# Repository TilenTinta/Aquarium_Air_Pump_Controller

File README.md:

# Aquarium_Air_Pump_Controller

Simple electronics for controlling aquarium air pump speed with some additional functions built around the WCH **CH32V003F4U6** MCU

---

## Table of Contents

- [Overview](#overview)
- [Features](#features)
  - [Hardware](#hardware)
  - [Software](#software)
- [Mounting](#mounting)
- [Flashing Firmware](#flashing-firmware)
- [Working device](#working-device)
  - [Working Principle](#working-principle)
- [Debugging](#debugging)
  - [LED Status Codes](#led-status-codes)

---

## Overview

This controller is a very compact solution for controling aquarium air pump speed. It is meant to be mounted on the back side of cheap chinese pumps that uses DC brushed motors like **PXYP370** and are powered from USB. By adjusting potenciometer on PCB you can tune pump speed and by that the amount of air provided in aquarium/filter. If you want to control this pump from external device like **ESP32** you can connect it over UART pads. This allow you to monitor and control the pump.

---

## Features

### Hardware

- **MCU:** WCH **CH32V003F4U6** with SWIO. 
- **Power:** Directly from 5V - USB.
- **Power regulation:** N-Channel MOSFET AP30N03DF.
- **Adjustment:** Duty cycle with potenciometer
- **Sensors:** Voltage IN, temperature.
- **Indicators/Controls:** Status LED and UART. 

### Software

- **Firmware:** C, developed in **MounRiver Studio IDE**. 
- **Updates:** **Custom bootloader** supports UART firmware updates. 

---

## Mounting

To mount controller on air pump you first need to remove silicon housing from the pump. Desolder both wires and bleed resistor from the motor contacts and clean them. Then solder the wires from USB cable to PCB. Correctly oriented pcb can be then soldered directly on motor contacts.

---

## Flashing Firmware

- Open the project in **MounRiver Studio IDE**, compile, and **upload** to the **CH32V003F4U6** MCU. 

> The board also includes a **custom bootloader** for **UART firmware updates** when supported by the desktop toolchain. 

---

## Working device

When USB cable is pluging the controler goes thrue start up routine. After that if everything is okay (input voltage, temperatue) it goes in running mode, otherwise it falls in error state which is indicated with **solid red light**.

### Working Principle

- **Sampling:** The system samples data at 50Hz*. In the first sample, the MCU collects raw measurements. In the next sample, these values are converted into real-world units (V, °C, %). This results in an effective sampling rate of 25Hz for the calculated values.
- **Control Logic:** Based on the collected values, the controller can either trigger an error or set a new duty cycle for the motor based on the potentiometer reading.
- **Error Conditions:**
    - **Over-temperature:** 80°C
    - **Under-voltage:** 3.5V
- **Duty Cycle:** The duty cycle can be set between 10% and 90%. Values below 10% are treated as 0%, and values above 90% are treated as 100%.
    - **Note:** This DC motors require a minimum of 3.0V - 3.5V to start.

---

## Debugging

### LED Status Codes  

| LED Pattern     | Meaning                   |
|-----------------|---------------------------|
| Blinking **red**  | Device initialization   |
| Solid **red**     | Device error            |

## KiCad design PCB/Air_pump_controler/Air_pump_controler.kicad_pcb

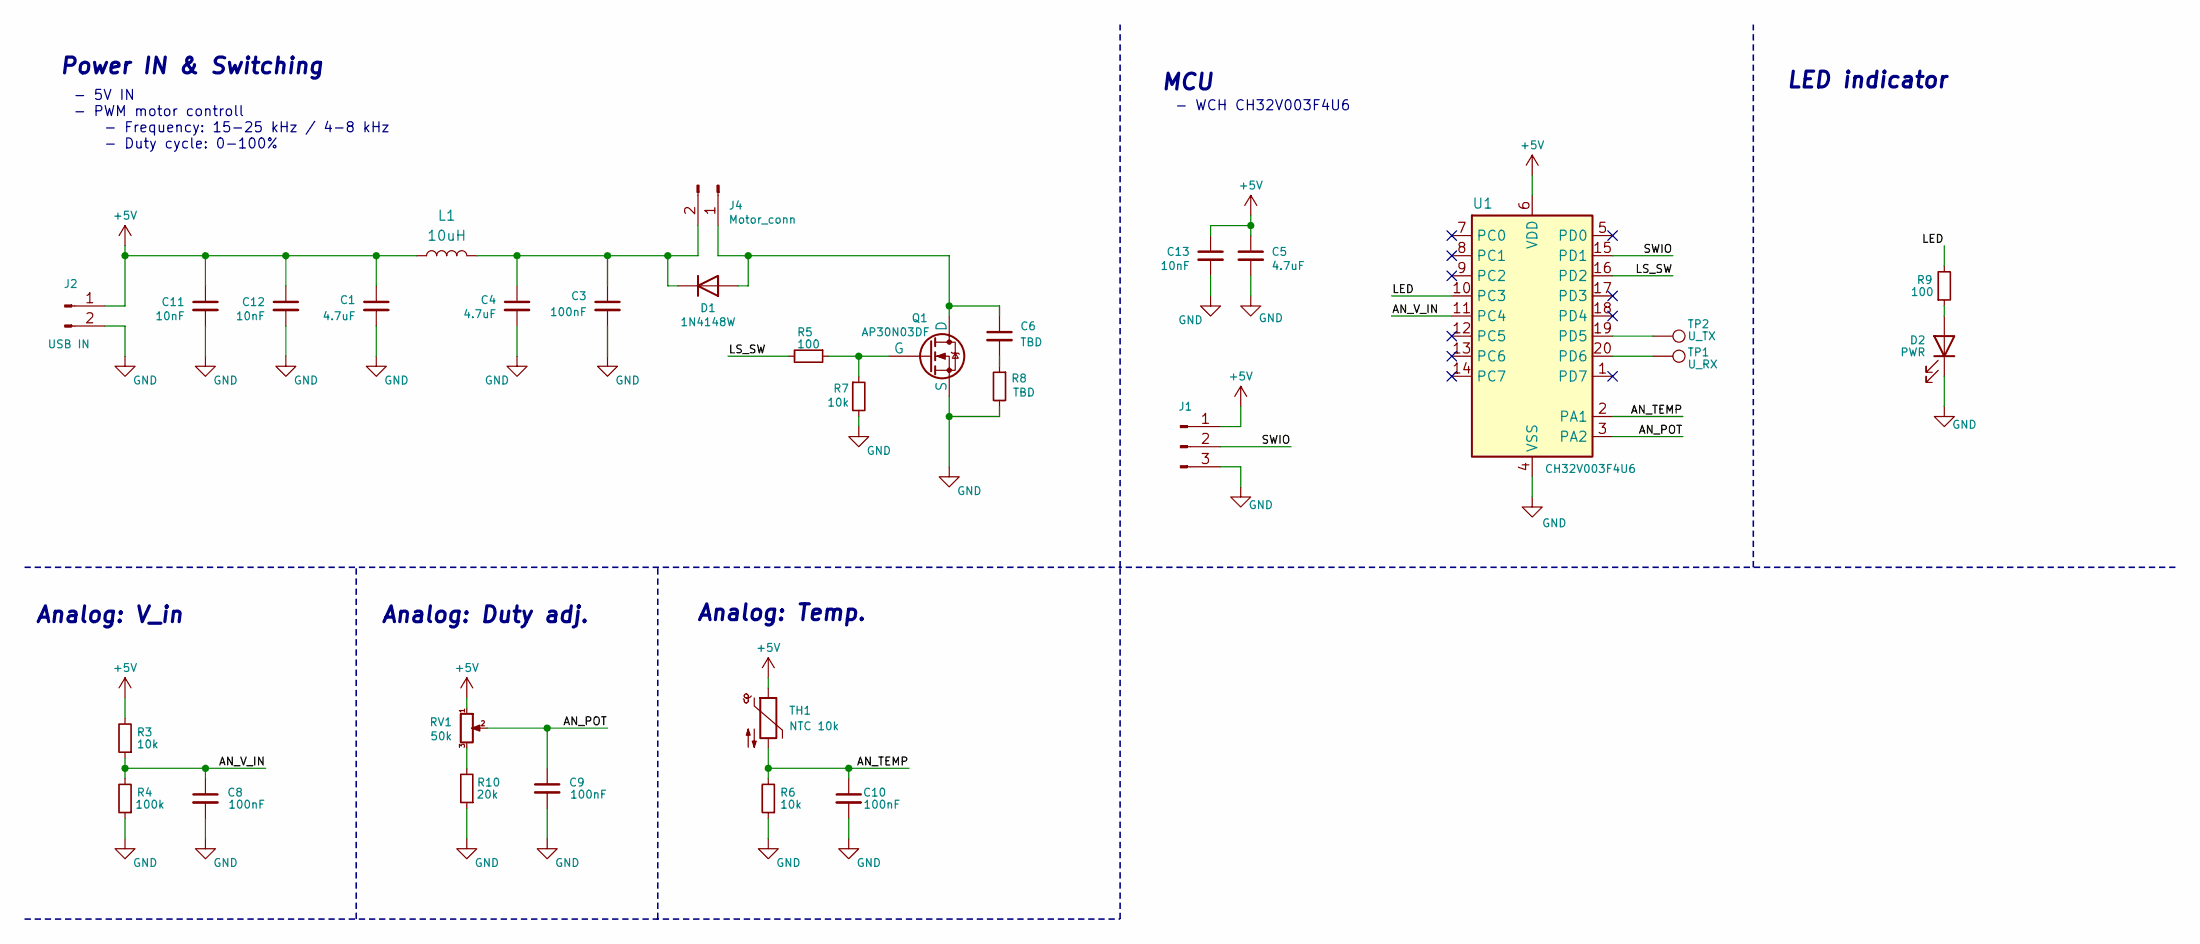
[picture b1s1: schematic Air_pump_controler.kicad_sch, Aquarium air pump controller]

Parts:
C1, C4: 4.7uF; C_1206_3216Metric
C3, C8, C9, C10: 100nF; C_0603_1608Metric
C5: 4.7uF; C_0402_1005Metric
C6: TBD; C_0603_1608Metric
C11, C12, C13: 10nF; C_0402_1005Metric
D1: 1N4148W; D_SOD-123
D2: PWR; LED_0603_1608Metric
J1: Conn_01x03_Pin; Samtec_UMPS-03-XX.X-X-V-S_1x03_P2.0mm_Socket
J2: USB IN; PinHeader_1x02_P2.54mm_Vertical
J4: Motor_conn
L1: 10uH; L_APV_APH0420
Q1: AP30N03DF
R3, R6, R7: 10k; R_0603_1608Metric
R4: 100k; R_0603_1608Metric
R5, R9: 100; R_0603_1608Metric
R8: TBD; R_0603_1608Metric
R10: 20k; R_0603_1608Metric
RV1: 50k; Potentiometer_Bourns_TC33X_Vertical
TH1: NTC 10k; R_0603_1608Metric
TP1: U_RX; TestPoint_Pad_D1.0mm
TP2: U_TX; TestPoint_Pad_D1.0mm
U1: CH32V003F4U6; QFN-20-1EP_3x3mm_P0.4mm_EP1.65x1.65mm

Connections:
+5V: C1.1, C5.1, C11.1, C12.1, C13.1, J1.1, J2.1, L1.1, R3.2, RV1.1, TH1.1, U1.6 (VDD)
/AN_POT: C9.1, RV1.2, U1.3 (PA2)
/AN_TEMP: C10.1, R6.2, TH1.2, U1.2 (PA1)
/AN_V_IN: C8.1, R3.1, R4.2, U1.11 (PC4)
/LED: R9.2, U1.10 (PC3)
/LS_SW: R5.2, U1.16 (PD2)
/SWIO: J1.2, U1.15 (PD1)
GND: C1.2, C3.2, C4.2, C5.2, C8.2, C9.2, C10.2, C11.2, C12.2, C13.2, D2.1 (K), J1.3, J2.2, Q1.1 (S), R4.1, R6.1, R7.2, R8.2, R10.1, U1.4 (VSS), U1.21 (VSS)
unnamed: C6.2, R8.1
unnamed: C6.1, D1.2 (A), J4.1, Q1.3 (D)
unnamed: C3.1, C4.1, D1.1 (K), J4.2, L1.2
unnamed: D2.2 (A), R9.1
unnamed: Q1.2 (G), R5.1, R7.1
unnamed: R10.2, RV1.3
unnamed 14: TP2.1, U1.19 (PD5); also elsewhere on the board
unnamed 15: TP1.1, U1.20 (PD6); also elsewhere on the board

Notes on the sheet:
Analog: Duty adj.
- 5V IN - PWM motor controll - Frequency: 15-25 kHz / 4-8 kHz - Duty cycle: 0-100%
LED indicator
Analog: Temp.
- WCH CH32V003F4U6
Analog: V_in
Power IN & Switching
MCU

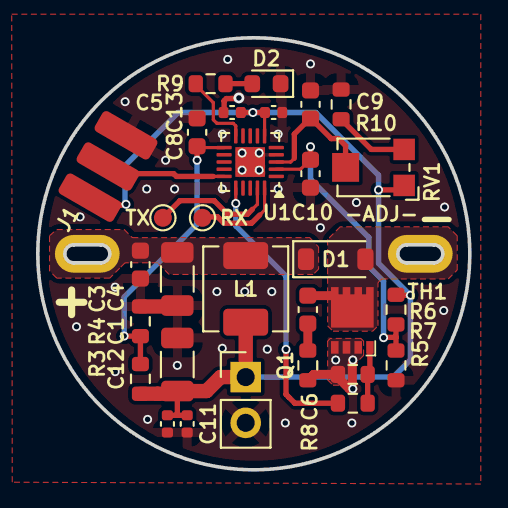
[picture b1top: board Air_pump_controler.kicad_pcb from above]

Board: 2 copper layers, 24.0 x 24.0 mm, 31 parts (0 on the bottom side), 16 nets.

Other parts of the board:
RX: U_RX; TestPoint_Pad_D1.0mm
TX: U_TX; TestPoint_Pad_D1.0mm

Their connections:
unnamed 14: TX.1; also elsewhere on the board
unnamed 15: RX.1; also elsewhere on the board

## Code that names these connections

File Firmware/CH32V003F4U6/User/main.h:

/***************************************************************************
 * File Name          : main.h
 * Author             : Tinta T.
 * Version            : V1.0.0
 * Date               : 2025/10/16
 * Description        : Main header file of Aquarium air pump controller
***************************************************************************/

#ifndef USER_MAIN_H_
#define USER_MAIN_H_

/* Includes */
#include <stdio.h>
#include <stdint.h>
#include <string.h>

/*###########################################################################################################################################################*/
/* Defines */

// Device constants
#define DEVICE_NAME    "Pump control"   // Name of the device
#define SW_VER              1           // Software version (used in UART packets)
#define SW_DATE        "October 2025"   // Date of software

#define OVER_TEMP           80          // Over temperature protection
#define BASE_VOLTAGE        500         // Expected voltage on the input
#define UNDER_VOLT          350         // Under voltage protection (3.5V)
#define MIN_DUTY            10          // Minimum value of duty cycle (lower is 0)
#define MAX_DUTY            90          // Maximum value of duty cycle (higher is 100)
#define V_IN_R1             10000       // Voltage divider (input voltage) R1 
#define V_IN_R2             100000      // Voltage divider (input voltage) R2 
#define DUTY_VREF           5           // Duty cycle ideal reference voltage
//#define DUTY_POT          20000       // Potenciometer (duty cycle), PCB Rev.: 0.1
#define DUTY_POT            50000       // Potenciometer (duty cycle), PCB Rev.: 0.2
#define DUTY_R              1800        // Resistor R2 (duty cycle), PCB Rev.: 0.2
#define TEMP_BETA           39500       // Voltage divider (temperature) NTC Beta value
#define TEMP_R0             10000       // R_0 value of NTC
#define TEMP_R              10000       // Voltage divider (temperature) R2 
#define TEMP_T_0            29815       // T_0 - reference temperature 25C / 298.15K

// Pinout
#define LED_RED             GPIO_Pin_3  // PC3: Pin of red LED
#define LS_SW               GPIO_Pin_2  // PD2: Low side switching mosfet
#define USART_TX            GPIO_Pin_5  // PD5: UART TX
#define USART_RX            GPIO_Pin_6  // PD6: UART RX
#define AN_V_IN             GPIO_Pin_4  // PC4: Analog read - USB voltage
#define ADC_CH_V_IN         ADC_Channel_2   // ADC Channel of PC4
#define AN_TEMP             GPIO_Pin_1  // PA1: Analog read - Temperature
#define ADC_CH_TEMP         ADC_Channel_1   // ADC Channel of PA1
#define AN_POT              GPIO_Pin_2  // PA2: Analog read - Potenciomeret voltage
#define ADC_CH_POT          ADC_Channel_0   // ADC Channel of PA2

/*###########################################################################################################################################################*/
/* Structs - marked with s at the beginning*/

typedef struct {
    uint8_t     bootDone;               // Flag: signal end of device initialization
    uint8_t     state;                  // Main state machine variable   
    uint8_t     analog_state;           // Analog read state machine variable  
    uint8_t     flag_analog_state;      // Flag used in IRQ for state monitoring
    uint8_t     flag_adc_read;          // Flag: read ADC value from current channel
    uint8_t     flag_overtemp;          // Flag: overtemperature protection
    uint8_t     flag_undervoltage;      // Flag: undervoltage protection
    uint16_t    duty;                   // Value if current duty cycle
} S_DEVICE;

typedef struct {            
    uint16_t    adcResults[3];          // buffer for ADC DMA results
    uint16_t    analogVoltage;          // Raw analog value of input voltage (10bit)
    uint16_t    analogTemperature;      // Raw analog value of temperature (10bit)
    uint16_t    analogPotenciometer;    // Raw analog value of potenciometer (10bit)
    uint16_t    voltage;                // Current value of input voltage
    uint16_t    temperature;            // Current value of temprature
    uint16_t    potVal;                 // Current value of potenciometer
    uint16_t    potPercent[10];         // Array of measurements from potenciometers
} S_ANALOG;


// Enumerate of states used in main state machine
enum eMainStates {
    devBoot,
    running,
    error
};

// Enumerate of states used in analog read state machine
enum eAnalogStates {
    ADCread,
    compute
};


#endif /* USER_MAIN_H_ */

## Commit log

2025-10-13 First commit
    PCB started, PCB edge
2025-10-14 Update
    PCB shematic and layout done rev.:0.1
2025-10-15 Finished PCB
2025-10-18 Readme
2025-10-18 Update
    readme
2025-10-19 Update
    software
2025-10-23 Update
    first FW complete, not tested on PCB
2025-11-02 Update
    pcb assembled, firmware works, added images
2025-11-05 Update
    modified potenciometer to voltage divider
2025-11-05 Update
    updated shematic and layout sheets and SW
2025-11-06 Update
    input voltage compensation for duty cycle
2025-11-06 Update
    changed potenciometer voltage divider, added filter cap
2025-11-06 Update
    added filter cap on input
2025-11-06 Update
    new gerbers
